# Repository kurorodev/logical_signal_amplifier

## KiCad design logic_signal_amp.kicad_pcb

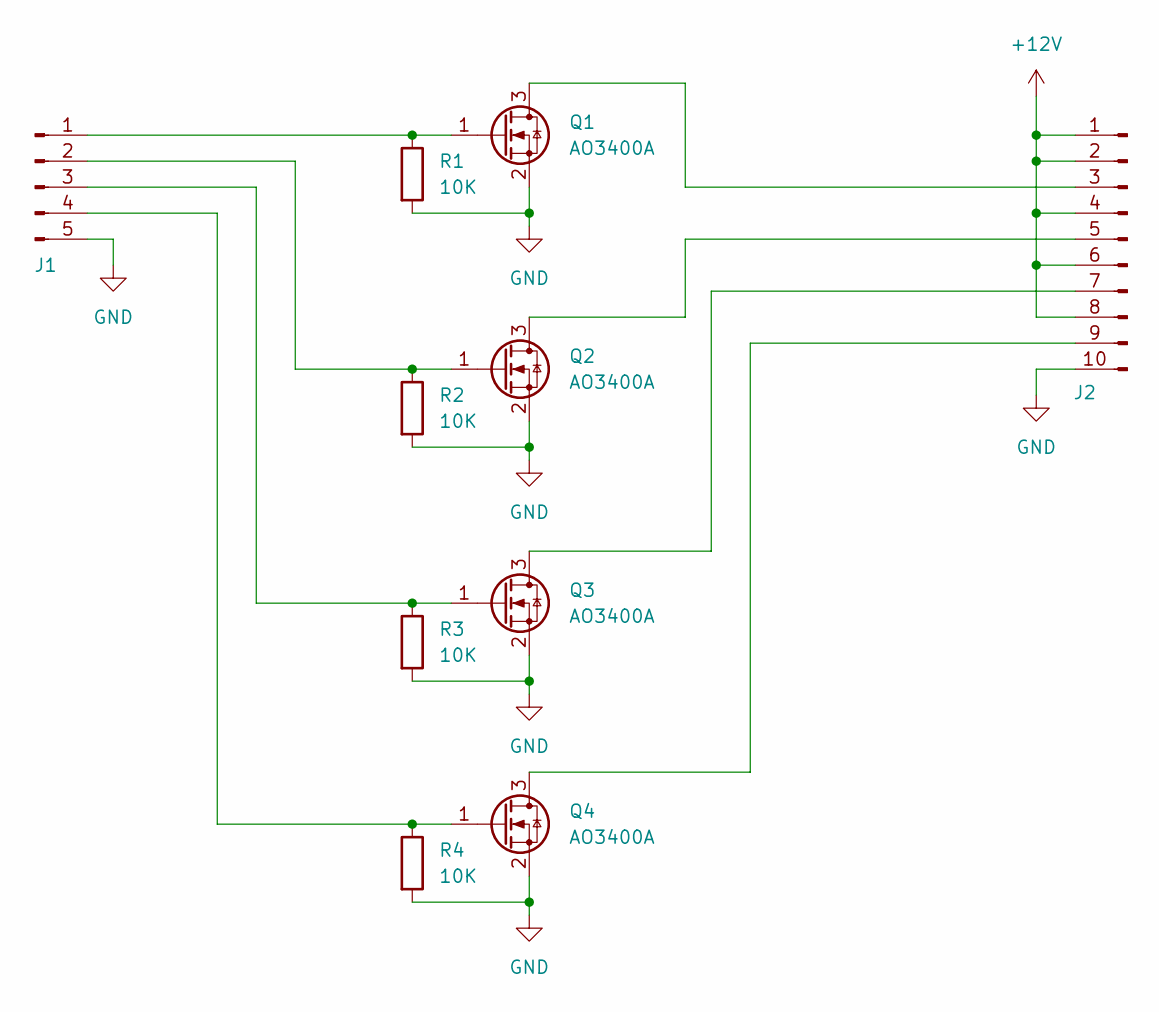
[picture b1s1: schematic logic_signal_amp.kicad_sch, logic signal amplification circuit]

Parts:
J1: Conn_01x05_Pin; PinHeader_1x05_P2.54mm_Vertical
J2: Conn_01x10_Pin; PinHeader_1x10_P2.54mm_Vertical
Q1, Q2, Q3, Q4: AO3400A; SOT-23
R1, R2, R3, R4: 10K; R_0805_2012Metric_Pad1.20x1.40mm_HandSolder

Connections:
+12V: J2.1, J2.2, J2.4, J2.6, J2.8
GND: J1.5, J2.10, Q1.2 (S), Q2.2 (S), Q3.2 (S), Q4.2 (S), R1.2, R2.2, R3.2, R4.2
unnamed: J1.1, Q1.1 (G), R1.1
unnamed: J1.2, Q2.1 (G), R2.1
unnamed: J1.3, Q3.1 (G), R3.1
unnamed: J1.4, Q4.1 (G), R4.1
unnamed: J2.3, Q1.3 (D)
unnamed: J2.5, Q2.3 (D)
unnamed: J2.7, Q3.3 (D)
unnamed: J2.9, Q4.3 (D)

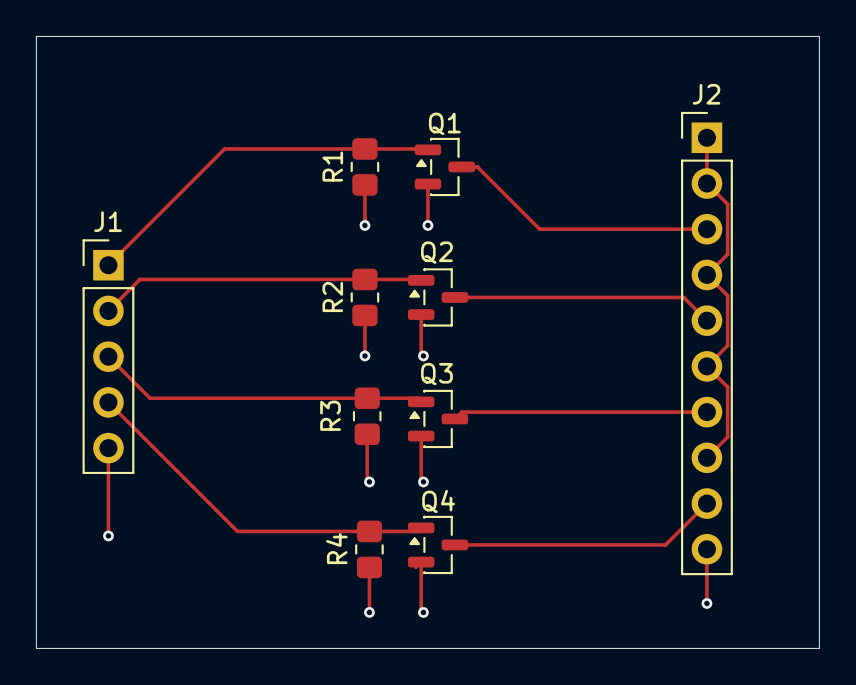
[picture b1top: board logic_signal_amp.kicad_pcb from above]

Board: 2 copper layers, 43.5 x 34.0 mm, 10 parts (0 on the bottom side), 10 nets.

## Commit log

2026-04-13 logic amp
2026-04-13 Add image to README for logical_signal_amplifier
2026-04-14 added PCB
2026-04-14 final PCB
2026-04-15 add readme
